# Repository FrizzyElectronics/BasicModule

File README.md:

# BasicModule
This module is one of the two basic modules that we created. This one was designed to hold a potentiometer, a 5mm LED, a 10mm LED, a Piranha LED or a buzzer. All of them on the same board.

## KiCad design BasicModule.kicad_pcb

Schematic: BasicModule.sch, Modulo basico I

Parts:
BZ1: Buzzer; Buzzer_12x9.5RM7.6
D1: LED; LED-5MM
M1: LED_PIRANHA_5MM
P1: CONN_01X03; JST_PH_S3B-PH-K_03x2.00mm_Angled
Q1: S8050; SOT-23
R1, R2: 1k; R_0805
RV1: POT; trimmer_alps-rk09k1130ah1

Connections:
+5V: P1.2, R2.2, RV1.1
GND: P1.3, Q1.3 (E), RV1.3
unnamed: BZ1.1 (-), D1.1 (K), M1.-, M1.R, Q1.2 (C)
unnamed: BZ1.2 (+), D1.2 (A), M1.B, M1.G, R2.1
unnamed: Q1.1 (B), R1.2
SIGNAL: P1.1, R1.1, RV1.2

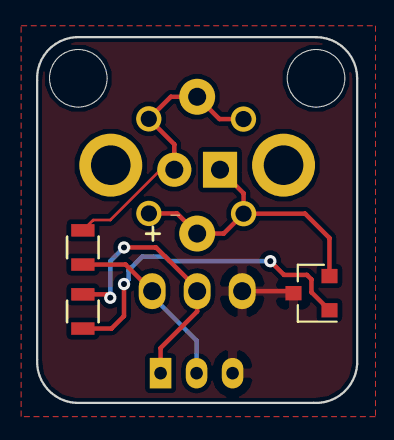
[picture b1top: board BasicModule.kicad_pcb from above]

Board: 2 copper layers, 17.8 x 20.3 mm, 8 parts (0 on the bottom side), 6 nets.

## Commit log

2017-05-01 License added
2017-05-01 Esquema terminado
2017-05-08 Se decide implementar el modulo solo para leds, buzzers y potenciometro
2017-05-08 Led piraña añadido al modulo
2017-05-08 LAyout Terminado
2018-01-20 Gerbers exportados
    Gerbers exportados para prueba de panelizacion
2018-02-04 Logo cambiado
2018-02-05 añadido nuevo logo
2018-02-10 Conector cambiado
2018-03-04 arbol de carpetas cambiado
2018-05-06 BOM exportado
2018-05-06 gerbers exportados
2018-07-10 Valor del transistor cambiado
2018-07-14 Re-rellenado el plano de masa
